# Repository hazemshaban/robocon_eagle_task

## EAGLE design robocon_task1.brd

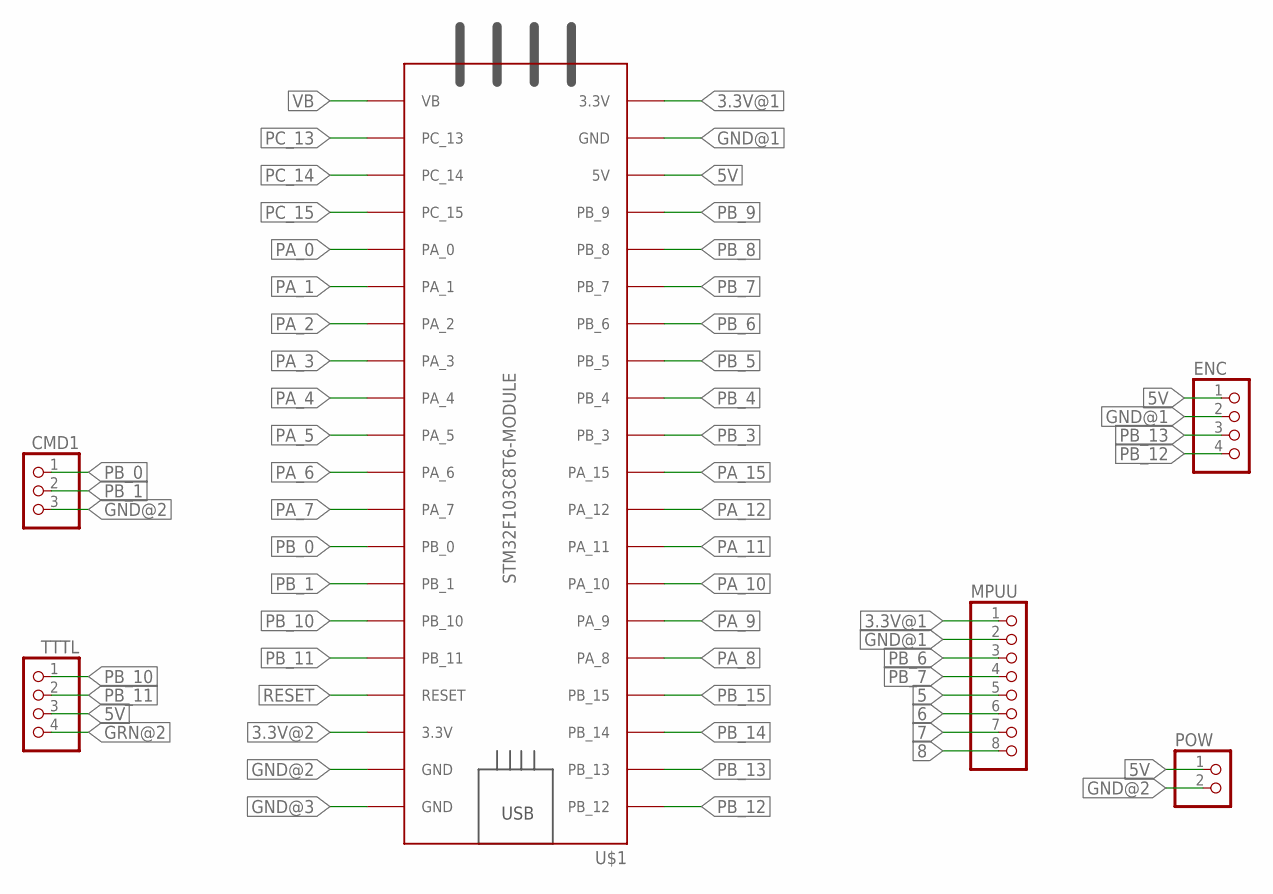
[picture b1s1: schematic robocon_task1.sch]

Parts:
CMD1: PINHD-1X3; 1X03
ENC: PINHD-1X4; 1X04
MPUU: PINHD-1X8; 1X08
POW: PINHD-2_DATA; 1X02_DATA
TTTL: PINHD-4_DATA; 1X04_DATA
U$1: STM32F103C8T6-MODULE

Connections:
3.3V@1: MPUU.1, U$1.3.3V_1 (3.3V)
3.3V@2: U$1.3.3V_2 (3.3V)
5: MPUU.5
5V: ENC.1, POW.1, TTTL.3, U$1.5V
6: MPUU.6
7: MPUU.7
8: MPUU.8
GND@1: ENC.2, MPUU.2, U$1.GND_1 (GND)
GND@2: CMD1.3, POW.2, U$1.GND_2 (GND)
GND@3: U$1.GND_3 (GND)
GRN@2: TTTL.4
PA_0: U$1.PA_0
PA_1: U$1.PA_1
PA_2: U$1.PA_2
PA_3: U$1.PA_3
PA_4: U$1.PA_4
PA_5: U$1.PA_5
PA_6: U$1.PA_6
PA_7: U$1.PA_7
PA_8: U$1.PA_8
PA_9: U$1.PA_9
PA_10: U$1.PA_10
PA_11: U$1.PA_11
PA_12: U$1.PA_12
PA_15: U$1.PA_15
PB_0: CMD1.1, U$1.PB_0
PB_1: CMD1.2, U$1.PB_1
PB_3: U$1.PB_3
PB_4: U$1.PB_4
PB_5: U$1.PB_5
PB_6: MPUU.3, U$1.PB_6
PB_7: MPUU.4, U$1.PB_7
PB_8: U$1.PB_8
PB_9: U$1.PB_9
PB_10: TTTL.1, U$1.PB_10
PB_11: TTTL.2, U$1.PB_11
PB_12: ENC.4, U$1.PB_12
PB_13: ENC.3, U$1.PB_13
PB_14: U$1.PB_14
PB_15: U$1.PB_15
PC_13: U$1.PC_13
PC_14: U$1.PC_14
PC_15: U$1.PC_15
RESET: U$1.RESET
VB: U$1.VB

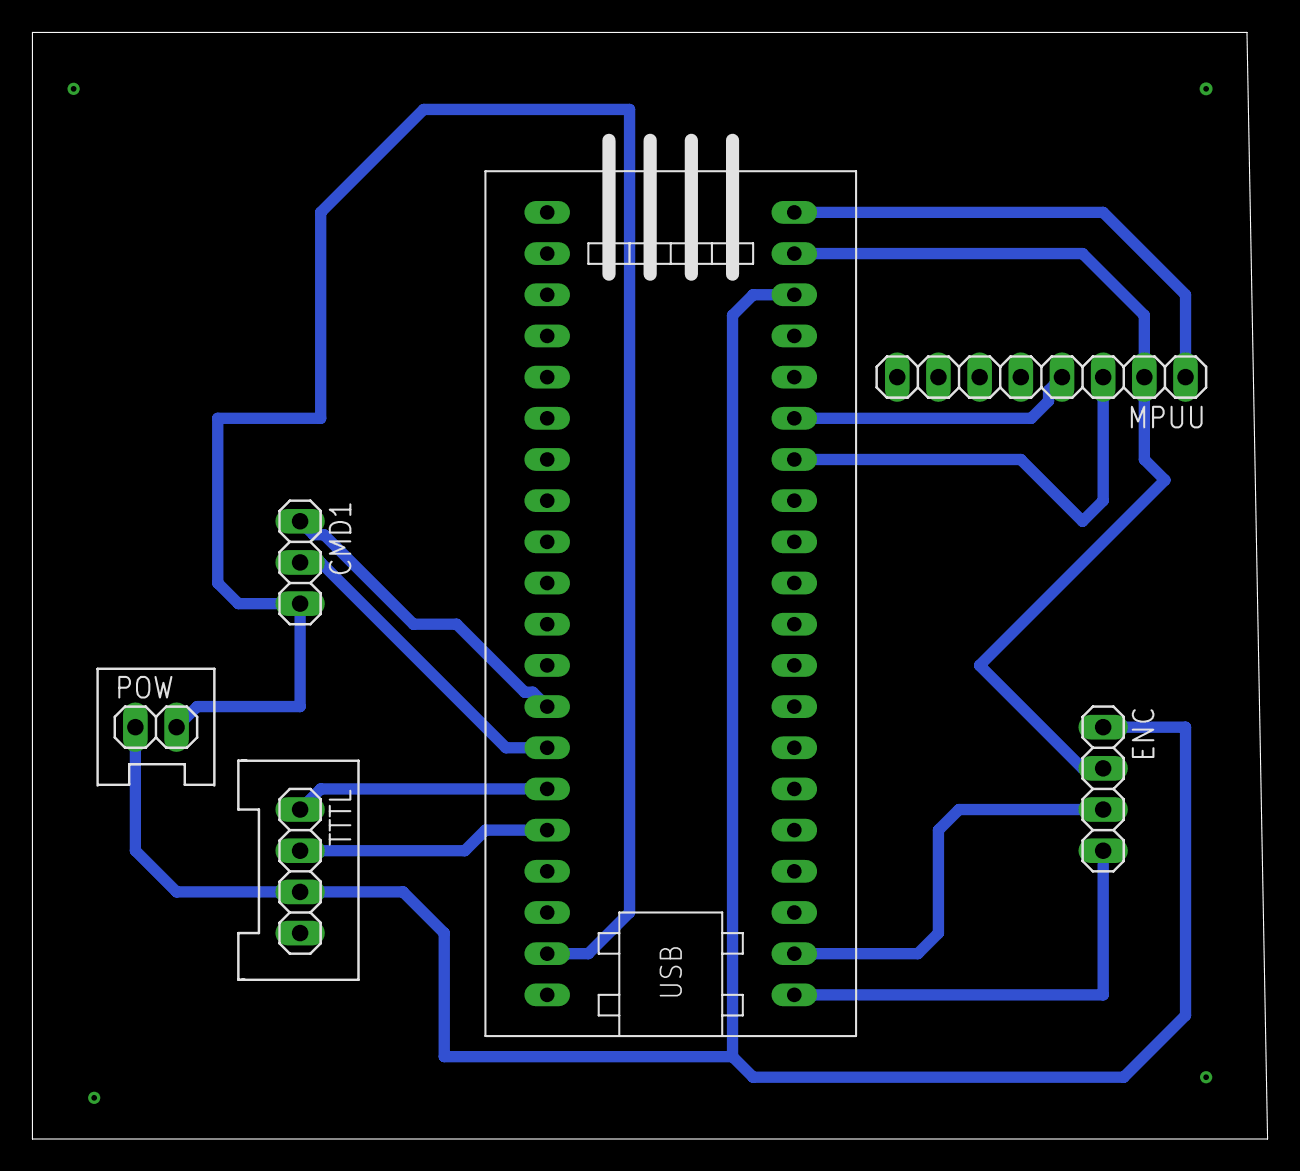
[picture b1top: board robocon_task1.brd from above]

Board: 2 copper layers, 76.2 x 68.2 mm, 6 parts (0 on the bottom side), 12 nets.
